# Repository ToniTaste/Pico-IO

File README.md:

# Pico-IO

Pico-IO ist eine Hardwarekomponente mit Sensoren und Aktoren. Sie
besteht aus einem Raspberry Pico, an dem sieben LED - beispielsweise zur
Anzeige von Ampeln oder eines Würfelergebnisses - und ein
Minilautsprecher (Buzzer) zur Ausgabe von Tönen angeschlossen sind. Drei
Sensoren führen zu den analogen Eingängen des Raspberry Pico und dienen
der Erfassung von Helligkeit, Tastendruck und Magnetfeldstärke.

|  |
|:----------------------------:|

Pico-IO lässt sich in Entwicklungsumgebungen für den Raspberry Pico block- und textbasiert programmieren. Das System wurde erfolgreich mit Microblocks, Mind+, Thonny (MicroPython), Arduino (C++) und Java getestet. Vier Beispiele liegen in den Sprachen vor.

Pico-IO wurde für die 16. Landestagung der GI-Fachgruppe „Informatische
Bildung in Mecklenburg-Vorpommern" 2025 entwickelt und allen
Fachgruppenmitgliedern kostenfrei zur Verfügung gestellt.

|  |
|:-------------------------------------------------:|

Pico-IO unterliegt der Creative Commons Licence CC BY-SA 4. Alle
Materialien, Schaltpläne und Bilder und Programmbeispiele stehen somit
unter einer freien Lizenz und auf der Webseite der Fachgruppe
„Informatische Bildung in MV" jedem zur Verfügung.

**Bei der Version für die Landestagung wurden alle Bauelemente
aufgelötet, jedoch nicht alle Lötpunkte gesetzt. Das Löten des
Mikrotasters und einer Steckleiste ist zu beenden.**

# Hardware

## Schaltplan

Die Schaltung wurde auf einem Breadboard aufgebaut, getestet und in KiCad übertragen. Die KiCad-Dateien liegen im Ordner Hardware. Den Schaltplan gibt es auch als [PDF-Dokument](Hardware/Schaltplan.pdf).

Das zentrale Element der Hardwarekomponente ist der steckbare Raspberry
Pi Pico H. Von diesem werden die Pins 20 bis 36 benutzt. Es können die
Version 1 und 2 des Pico (W)H verwendet werden.

|  |
|:------------------------------------------------:|

Pico-IO verfügt über drei Sensoren:

- GPIO 26: Tastsensor Wertebereich: \[\< 10, 1023\]
- GPIO 27: Magnetsensor Wertebereich: \[≈ 275 ... ≈ 825\], Normalwert: ≈ 555
- GPIO 28: Lichtsensor Wertebereich: \[\< 10 ... 1023\]

|  |
|:---------------------------------------:|

Pico-IO besitzt acht Aktoren:

- GPIO 16 ... 22: LED-Matrix
- GPIO 15: Tonausgabe über Buzzer

|  |
|:--------------------------------------:|

## Bauelemente

|  |
|:----------------------------------------:|

| Bauelement         | Name      | Wert                                |  Symbolbild           |
|--------------------|-----------|-------------------------------------|-----------------------|
|  LED               | D1 ... D7 |  2x rot, 2x gelb, 2x grün, 1x blau  |  |
|  Mikrotaster       | SW1       |  Kurzhubtaster 6x6                  |  |
|  Fototransistor    | T1        |  INL-5APT30                         |  |
|  Hallsensor        | IC1       |  AH49FZ3-G1                         |  |
|  Widerstandsnetz   | RN1       |  SIL 7-6 200 Ω                      |  |
|  Widerstand        | R1, R2    |  10 kΩ: braun - schwarz - orange    |  |
|  Widerstand        | R3        |  2,2 kΩ: rot - rot - rot            |  |
|  Widerstand        | R4        |  100 Ω: braun - schwarz - braun     |  |
|  Widerstand        | R5        |  1 kΩ: braun - schwarz - rot        |  |
|  Transistor        | T2        |  BC 547C                            |  |
|  Buzzer            | BZ1       |  CEM 1203                           |  |
|  Steckleiste       |           |  1x20-polig                         |  |
|  Raspberry Pi Pico |           |  Raspberry Pi Pico (W)H 1           |  |

Für Nachbauten sollten die Widerstandswerte für die LED-Matrix in Abhängigkeit von der Helligkeit und von der zulässigen Strombelastung
des GPIO-Ausgangs angepasst werden. Der Hallsensor sollte gegen ein Modell getauscht werden, das auch bei schwachen Magnetfeldern
unterscheidbare Messwerte liefert.

Die Kosten für die Bauelemente liegen bei ca. 7 bis 14 EUR in Abhängigkeit vom Mengenrabatt. 

## Platine

| Bestückungsseite                      | Lötseite                      |
|:-------------------------------------:|:-----------------------------:|
|  |  |

Die Platinen wurden in KiCad entwickelt. Im Hardware-Ordner liegen alle Daten vor. Im Falle einer Überarbeitung sollte die Anordnung der Anschlüsse von IC1 so geändert werden, dass Pin 2 am kürzesten ist.

Die Kosten für die Platine hängen stark vom Anbieter und der Menge ab.
Die 100 Platinen für die Landestagung kosteten seinerzeit incl. Versand,
Zoll und Steuern etwas über 50 EUR.

## Aufbau

### Werkzeug und Zubehör

- Lötkolben für elektronische Bauelemente
- Seitenscheider
- Flachzange
- Lötzinn 1 mm Durchmesser SN99 mit (möglichst wasserlöslichem) Flussmittel

Der Aufbau erfolgt vom flachsten zum höchsten Bauelement. Diese werden
auf der Bestückungsseite platziert und auf der Lötseite gelötet. Bei
bestimmten Bauelemente ist die Polung zu beachten.

### Hall-Sensor 

|  |
|:----------------------------------------:|

IC1 ist für die Erfassung der Magnetfeldstärke zuständig. Es handelt
sich um einen integrierten Schaltkreis, der keine Zusatzbeschaltung
benötigt. Seine Anschlüsse müssen so gebogen sein, dass er liegend
eingelötet werden kann. Die bedruckte schmale Fläche zeigt nach oben.
Zum Biegen sollte eine Flachzange verwendet werden.

### Widerstände

| R1: , R2: , R3: , R4: , R5:  |
|:----------------------------------------:|

R3 bis R5 begrenzen den Stromfluss auf zulässige Werte. R1 und R2 sorgen
an den Eingängen des Raspberry Pico als sog. Pull-Down-Widerstände für
definierte Eingangssignale. R1 bis R5 sind entsprechend ihrer
Werte/Codierung zu platziert.

### Widerstandsnetz

| Bauelement:  | interner Aufbau:  |
|:---------------------------------:|:---------------------------------------|

RN1 ist ein Widerstandsnetz und fasst mehrere Widerstände sternförmig
zusammen. So wird der Platzbedarf auf der Platine reduziert. Auf der
Beschriftungsseite des Bauelements markiert ein Punkt Pin 1 und somit
die Sternmitte. Dieser Pin gehört in das quadratisch umrandete Loch auf
der Platine.

### Taster

|  |
|:---------------------:|

Der Taster SW1 dient als Eingabesensor.

### Transistor

| Symbolbild:  | Bauelement im Schaltplan:  |
|:---------------------------------:|:-----------------------------------------------:|

Der Transistor T2 schaltet das Signal zum Buzzer und verhindert eine
Überlastung des Prozessors. Beim Einbau ist auf die korrekte Polung zu
achten. Die runde Seite des Gehäuses zeigt zu R4 und R5.

### Buzzer

|  |
|:----------------------:|

Der Buzzer BZ1 erzeugt bei Verwendung eines schwingenden
Spannungssignals eine Tonausgabe. Auf dem Buzzergehäuse befindet sich
ein Plus-Symbol. Der zugehörige PIN ist in den auf der Platine mit Plus
gekennzeichneten Anschluss zu stecken.

### LED

| Symbolbild:  | Bauelement im Schaltplan:  |
|-----------------------------------|-------------------------------------------------|

Die Leuchtdioden (LED) dienen der Ausgabe. Um Ampeln programmieren zu
können, ist als Farbfolge von D1 zu D3 und von D5 zu D7 jeweils rot -
gelb - grün zu wählen. Die blaue LED ist D4. Beim Einbau ist die Polung
zu beachten. Der Platinenaufdruck zeigt die abgeflachte Seite der LED
an.

### Fototransistor

| Symbolbild:  | Bauelement im Schaltplan:  |
|:----------------------------------:|:----------------------------------------------:|

Der Fototransistor T1 sieht wie eine LED im klaren Gehäuse aus. Es
handelt sich jedoch um einen Sensor, der den Strom in Abhängigkeit von
der Helligkeit fließen lässt. Für den Einbau muss er korrekt gepolt wie
im Aufdruck abgebildet eingelötet werden. Die abgeflachte Seite zeigt
nach rechts.

### Steckerleisten

|  |
|:---------------------:|

Die beiden Steckerleisten tragen den Raspberry Pi Pico H. Nach Abschluss
der Lötarbeiten kann der Pico eingesetzt werden. Dabei ist auf die
korrekte Ausrichtung zu achten. Der USB-Port befindet sich rechts über
den Widerständen R4 und R5.

### Raspberry Pi Pico (W)H

Der Raspberry Pi Pico ist ein kompakter und kostengünstiger
Mikrocontroller. Die Anschlüsse GP0 bis GP28 können sehr flexibel als
Ein- oder Ausgänge programmiert und genutzt werden.

Eine besondere Rolle hat die Taste BOOTSEL. Sie ermöglicht es, den
Raspberry Pi Pico in den Bootloader-Modus zu versetzen. Beim Drücken der
BOOTSEL-Taste während des Anschlusses an einen Computer erscheint der
Pico als USB-Massenspeicher. So kann Firmware oder lauffähige Systeme,
beispielsweise MicroPython oder das Arduino-Demo-Programm, einfach auf
den Mikrocontroller übertragen werden.

|  |
|:---------------------:|

# Programmierung

## Treiber

Aktuelle Betriebssysteme erkennen den Pico-IO automatisch.

## Blockbasierte Programmierung mit Microblocks.fun

Microblocks.fun ist über die gleichnamige Website als Online- und
Offline-Editor verfügbar.

Pico-IO benötigt eine Firmware. Diese ist vor der ersten Verwendung aus
Microblocks zu installieren. Im ⚙️-Menü wählt man dazu zunächst
„aktualisiere Firmware auf dem Board" und dann „RP 2040". Anschließend
ist den Anweisungen zu folgen.

Über die Blockkategorie „Pins" lassen sich die Aktoren und Sensoren des
Pico-IO nutzen. Module ermöglichen die Einbindung von Erweiterungen
beispielsweise zur Ausgabe von Klängen. Besonders elegant gelöst ist die
grafische Darstellung von Messwerten im Diagramm.

## Blockbasierte Programmierung mit Mind+

Mind+ kann blockbasiert in der Offline-Version ab 1.8.1 auf Pico-IO
zugreifen.

Pico-IO benötigt eine Firmware. Diese ist vor der ersten Verwendung aus
Mind+ heraus über das Menü „Verbinden" zu installieren. Aktuell
funktionieren einige Hardwarezugriffe nicht zuverlässig. Dies soll in
den nächsten Versionen jedoch behoben werden.

## Textbasierte Programmierung mit MicroPython in Thonny

Thonny ist ein Beispiel für eine textbasierte Entwicklungsumgebung.

Pico-IO benötigt eine Firmware (MicroPython). Diese ist vor der ersten
Verwendung aus Thonny heraus im Menü „Werkzeuge" 🡪 „Interpreter" 🡪
„MicroPython installieren oder aktualisieren" zu installieren. Unter
„variant" muss der Eintrag „Raspberry Pi Pico" gewählt wählen. Nach
erfolgreicher Installation muss im Interpreterfenster aus MicroPython
gewechselt werden.

## Textbasierte Programmierung mit C++ in der Arduino-IDE

Die Arduino-IDE lässt sich als textbasiertes Entwicklungssystem nutzen
und erzeugt zudem ausführbare UF2-Dateien, die dann auf das System
geladen werden können.

Die zusätzliche Board-Verwalter-URL
„<https://github.com/earlephilhower/arduino-pico/releases/download/global/package_rp2040_index.json>"
muss in den Einstellungen eingetragen und dann im Boardverwalter das
Paket \"Raspberry Pi RP2040 Boards\" von Earle F. Philhower, III
installiert werden. Anschließend ist per Bootloadermodus das Board nebst
Port zu wählen.

## Textbasierte Programmierung mit Java mind. Version 17 (unter Windows/Linux/macOS) beispielsweise mit BlueJ

Pico-IO benötigt eine [Firmware](Software/Java/Firmata), die mittels Arduino aus der Standard-Firmata generiert wurde. Diese ist vor der ersten Verwendung auf dem Pico zu installieren. Während des Anschlusses an einen Computer muss die Taste BOOTSEL gedrückt werden. Der Pico erscheint dann als USB-Massenspeicher. Nun wird die PicoIO.uf2-Datei auf das Laufwerk kopiert. Nach einem Neustart des Pico blinkt die Onboard-LED mehrfach und das System ist bereit. 

Damit aus Java heraus auf Pico-IO zugegriffen werden kann, sind einige [Bibliotheken](Software/Java/Bibliotheken) in Java einzubinden. 

- In BlueJ geht dies im Menü  „Werkzeuge" 🡪 „Einstellungen" 🡪 „Bibliotheken" 🡪 „Benutzerbibliotheken". Alternativ kann man auch im jeweiligen BlueJ-Projektordner einen Unterordner namens "+libs" anlegen und die Bibliotheken dort hinein kopieren. BlueJ findet diese dann stets automatisch.
- Im JavaEditor erreicht man Einbindung über „Fenster" 🡪 „Konfiguration" 🡪 „Classpath User". Dort sind die Bibliotheken aus dem Ordner anzugeben.

Der Quelltext der Hauptbibliothek PicoIO.java befindet sich im Ordner [Source](Software/Java/Source). Sie verfügt über nachfolgende Methoden.

## Anwendungsbeispiele

In den Unterlagen zum Projekt finden sich vier [Anwendungsbeispiele](Software/), die
in Microblock, MicroPython, Mind+, Arduino und Java programmiert wurde. Das
Demo-Programm, welches auch das Schummelwürfelspiel umfasst, wurde mit
der Arduino-IDE entwickelt, liegt aber auch in Python vor.

(1) **Fensteralarm (Aktor: Buzzer; Sensor: Magnetstärke)**\
    Ein Alarmsignal wird ausgelöst, sobald der Fenstermagnet vom
    Fenstersensor entfernt wird.

(2) **Dämmerungslichtautomat (Aktor: LED, Sensor: Fototransistor)**\
    Fällt die Helligkeit unter einen bestimmten Grenzwert, so wird die
    Straßenbeleuchtung aktiviert. Während der Dämmerung ist das Licht
    der Lampe gedimmt.

(3) **Bedarfsampel (Aktor: LED; Sensor: Taster)**\
    Ein ampelgeschalteter Fußgängerüberweg wird gesteuert. Die
    Straßenampel wechselt systematisch auf Rot, wenn der Fußgänger am
    Knopf seinen Bedarf gemeldet hat. Die zugehörige Fußgängerampel
    schaltet auf grün. Nach einer Überquerungszeit wechseln die Ampeln
    in den Ausgangszustand zurück.

(4) **Schummelwürfel (Aktor: LED, Buzzer; Sensor: Taster, Magnetstärke,
    Fototransistor)**\
    Falls es nicht zu hell ist, sind Glücksspiele erlaubt. Ein Druck
    auf den Taster wirft einen virtuellen Würfel und zeigt das Ergebnis
    auf dem LED-Feld an. Wird ein Magnet an den Magnetsensor gelegt, ist
    das Würfelergebnis immer eine sechs.

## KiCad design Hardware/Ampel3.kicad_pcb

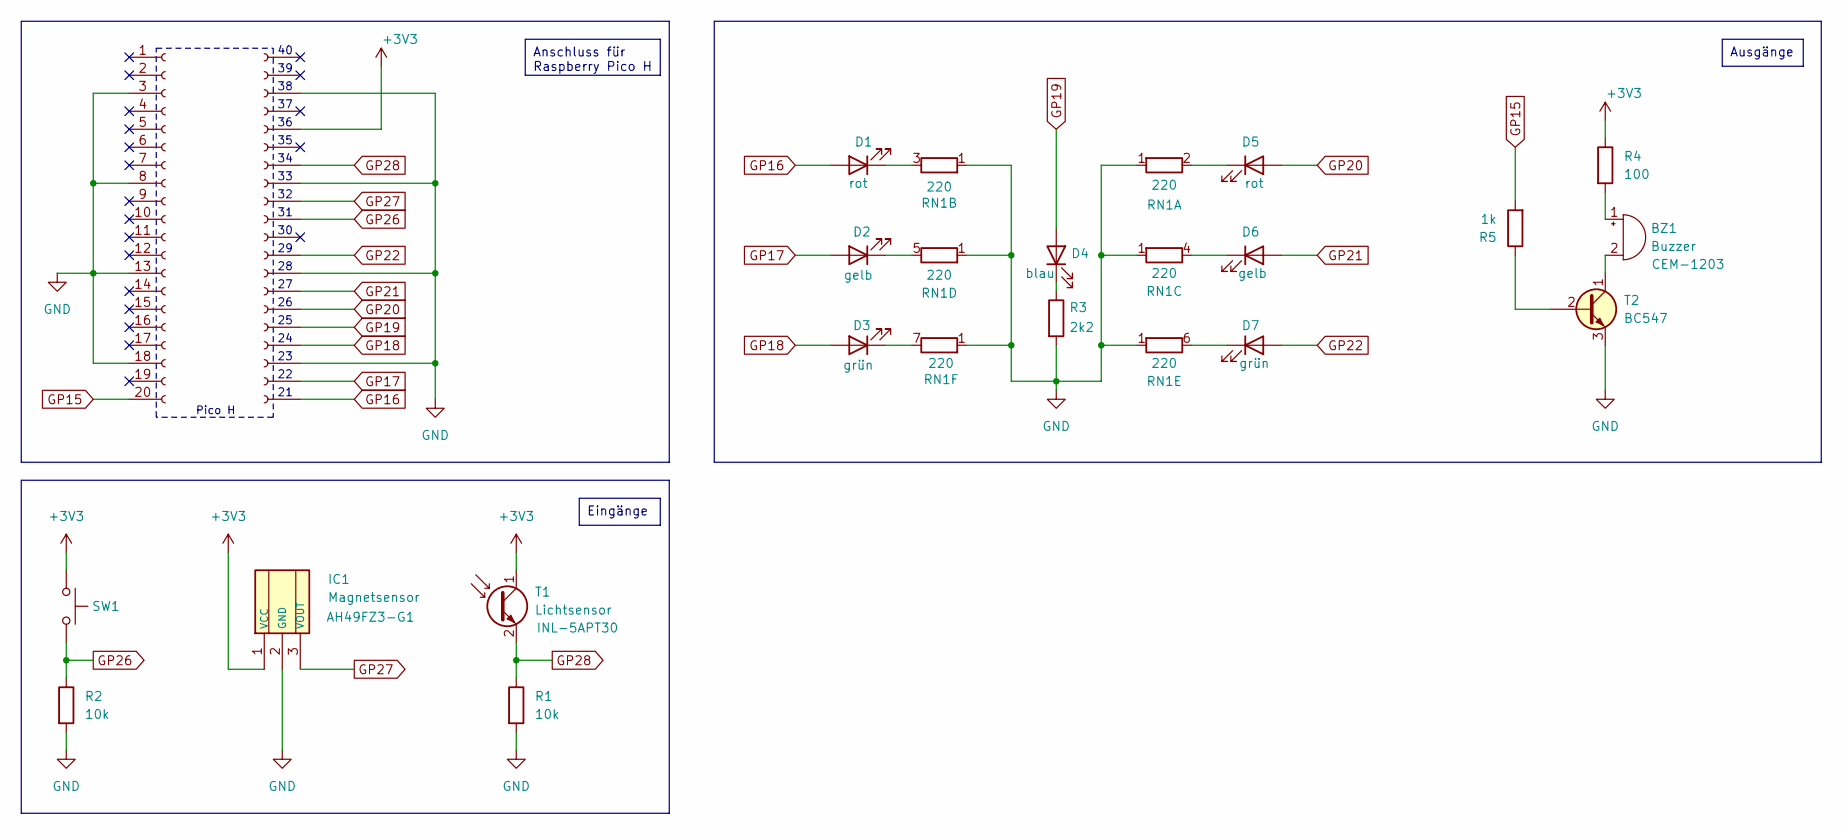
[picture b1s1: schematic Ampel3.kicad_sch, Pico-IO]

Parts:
BZ1: Buzzer; Buzzer_12x9.5RM6.5
D1: GP16; LED_D5.0mm
D2: GP17; LED_D5.0mm
D3: GP18; LED_D5.0mm
D4: GP19; LED_D5.0mm
D5: GP20; LED_D5.0mm
D6: GP21; LED_D5.0mm
D7: GP22; LED_D5.0mm
IC1: Magnetsensor; TO-92_Inline_Horizontal2_lötsicher; Manufacturer_Part_Number A1222LUA-T
Pico_L1: Conn_01x20_Socket; PinSocket_1x20_P2.54mm_Vertical
Pico_R1: Conn_01x20_Socket; PinSocket_1x20_P2.54mm_Vertical
R1, R2: 10k; R_Axial_DIN0207_L6.3mm_D2.5mm_P10.16mm_Horizontal
R3: 2k2; R_Axial_DIN0207_L6.3mm_D2.5mm_P10.16mm_Horizontal
R4: 100; R_Axial_DIN0207_L6.3mm_D2.5mm_P10.16mm_Horizontal
R5: 1k; R_Axial_DIN0207_L6.3mm_D2.5mm_P10.16mm_Horizontal
RN1: 220; R_Array_SIP7
SW1: Taster; SW_PUSH_6mm
T1: Lichtsensor; LED_D5.0mm_Clear
T2: BC547; TO-92_Inline_Wide

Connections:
+3V3: IC1.1 (VCC), Pico_R1.5, R4.1, SW1.1, T1.1 (C)
GND: IC1.2 (GND), Pico_L1.3, Pico_L1.8, Pico_L1.13, Pico_L1.18, Pico_R1.3, Pico_R1.8, Pico_R1.13, Pico_R1.18, R1.2, R2.2, R3.2, RN1.1 (R1), T2.3 (E)
GP15: Pico_L1.20, R5.2
GP16: D1.2 (A), Pico_R1.20
GP17: D2.2 (A), Pico_R1.19
GP18: D3.2 (A), Pico_R1.17
GP19: D4.2 (A), Pico_R1.16
GP20: D5.2 (A), Pico_R1.15
GP21: D6.2 (A), Pico_R1.14
GP22: D7.2 (A), Pico_R1.12
GP26: Pico_R1.10, R2.1, SW1.2
GP27: IC1.3 (VOUT), Pico_R1.9
GP28: Pico_R1.7, R1.1, T1.2 (E)
unnamed: BZ1.1 (+), R4.2
unnamed: BZ1.2 (-), T2.1 (C)
unnamed: D1.1 (K), RN1.3 (R2.2)
unnamed: D2.1 (K), RN1.5 (R4.2)
unnamed: D3.1 (K), RN1.7 (R6.2)
unnamed: D4.1 (K), R3.1
unnamed: D5.1 (K), RN1.2 (R1.2)
unnamed: D6.1 (K), RN1.4 (R3.2)
unnamed: D7.1 (K), RN1.6 (R5.2)
unnamed: R5.1, T2.2 (B)

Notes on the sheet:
Eingänge
Ausgänge
Anschluss für Raspberry Pico H
Pico H

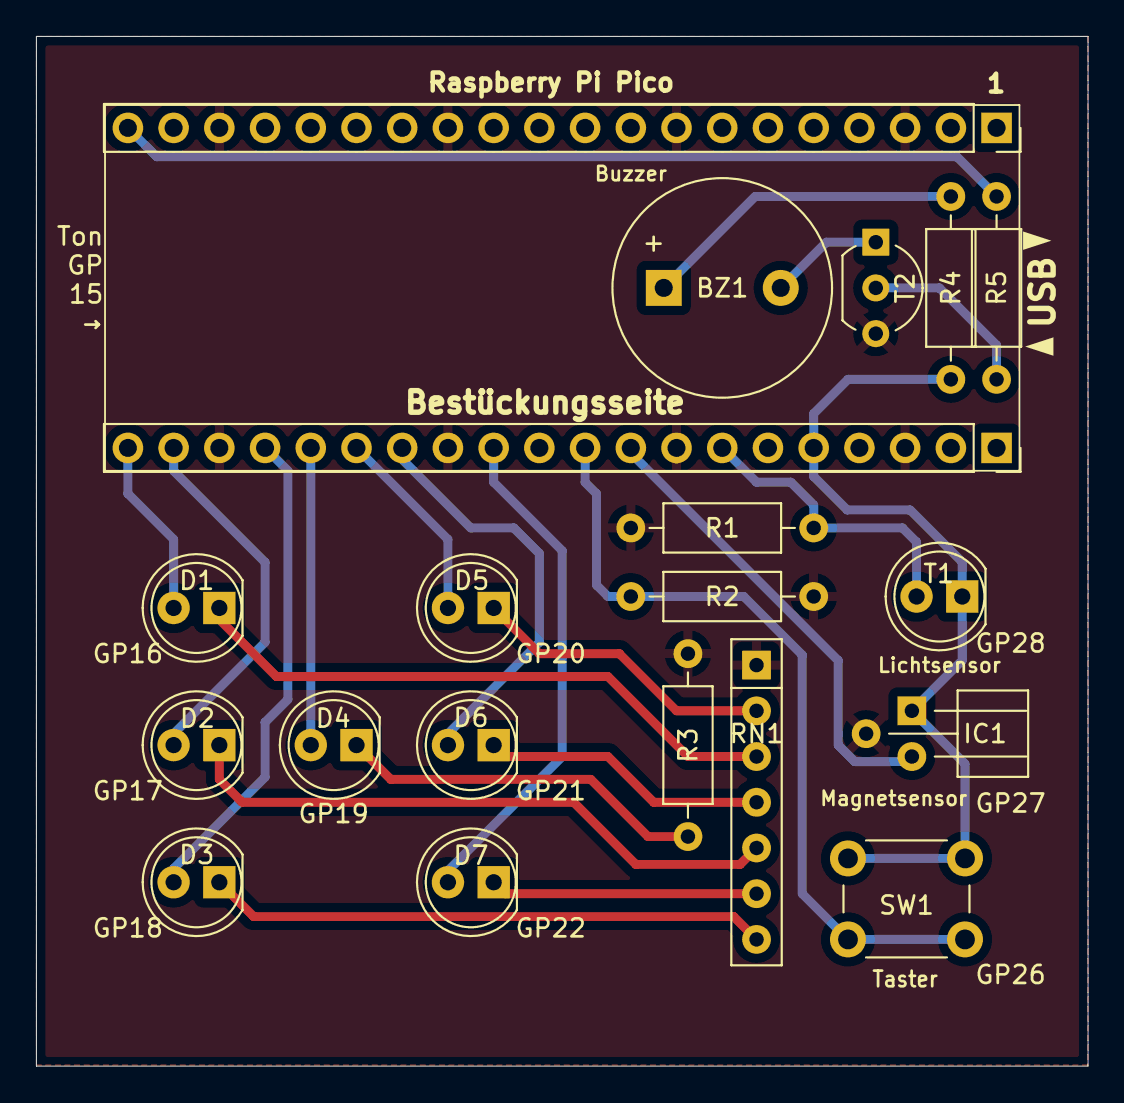
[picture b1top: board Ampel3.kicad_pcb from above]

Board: 2 copper layers, 58.4 x 57.2 mm, 20 parts (0 on the bottom side), 23 nets.

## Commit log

2025-02-05 Beschreibung/Dokumentation
    Aktuell noch in Word, eine Umwandlung in odt und PDF folgt.
2025-02-05 Upload Version 1
2025-02-05 init
2025-02-06 Fehlerkorrektur
2025-02-06 unnötigen Klangblock entfernt
2025-02-06 kleine Fehlerkorrekturen
2025-02-06 Gerber-Daten
2025-02-07 Anpassung an andere Sprachen
2025-02-07 Anpassungen an andere Sprachen
2025-02-07 Erweiterung Arduino
2025-02-07 Erweiterungen Arduino
2025-02-10 Update README.md
    Erweiterung um Java
2025-02-10 Java-Erweiterung
2025-02-11 Vervollständigung der Beispiele für Java
2025-02-12 Fehlerkorrektur
    Loops wurden fehlerhaft beendet bzw. liefen trotz Abbruch weiter. Das Problem wurde behoben.
2025-02-12 Fehlerbehebung
    Loops wurden nicht korrekt abgebrochen.
2025-02-18 Fehlerkorrektur - Anpassung an macOS/Linux (ungetestet)
2025-02-18 Anpassung an neue PicoIO-Klasse
2025-02-18 Anpassung an macOS
2025-02-23 Anpassungen für Linux/Windows/MacOS
2025-11-24 Enhance PicoIO with connection checks and calibration
    Refactor PicoIO class to improve connection handling and add calibration methods.

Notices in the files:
Hardware/Ampel3.kicad_pcb:
CC BY-SA 4.0 Tino Hempel
Hardware/Ampel3.kicad_sch:
CC BY-SA 4.0
